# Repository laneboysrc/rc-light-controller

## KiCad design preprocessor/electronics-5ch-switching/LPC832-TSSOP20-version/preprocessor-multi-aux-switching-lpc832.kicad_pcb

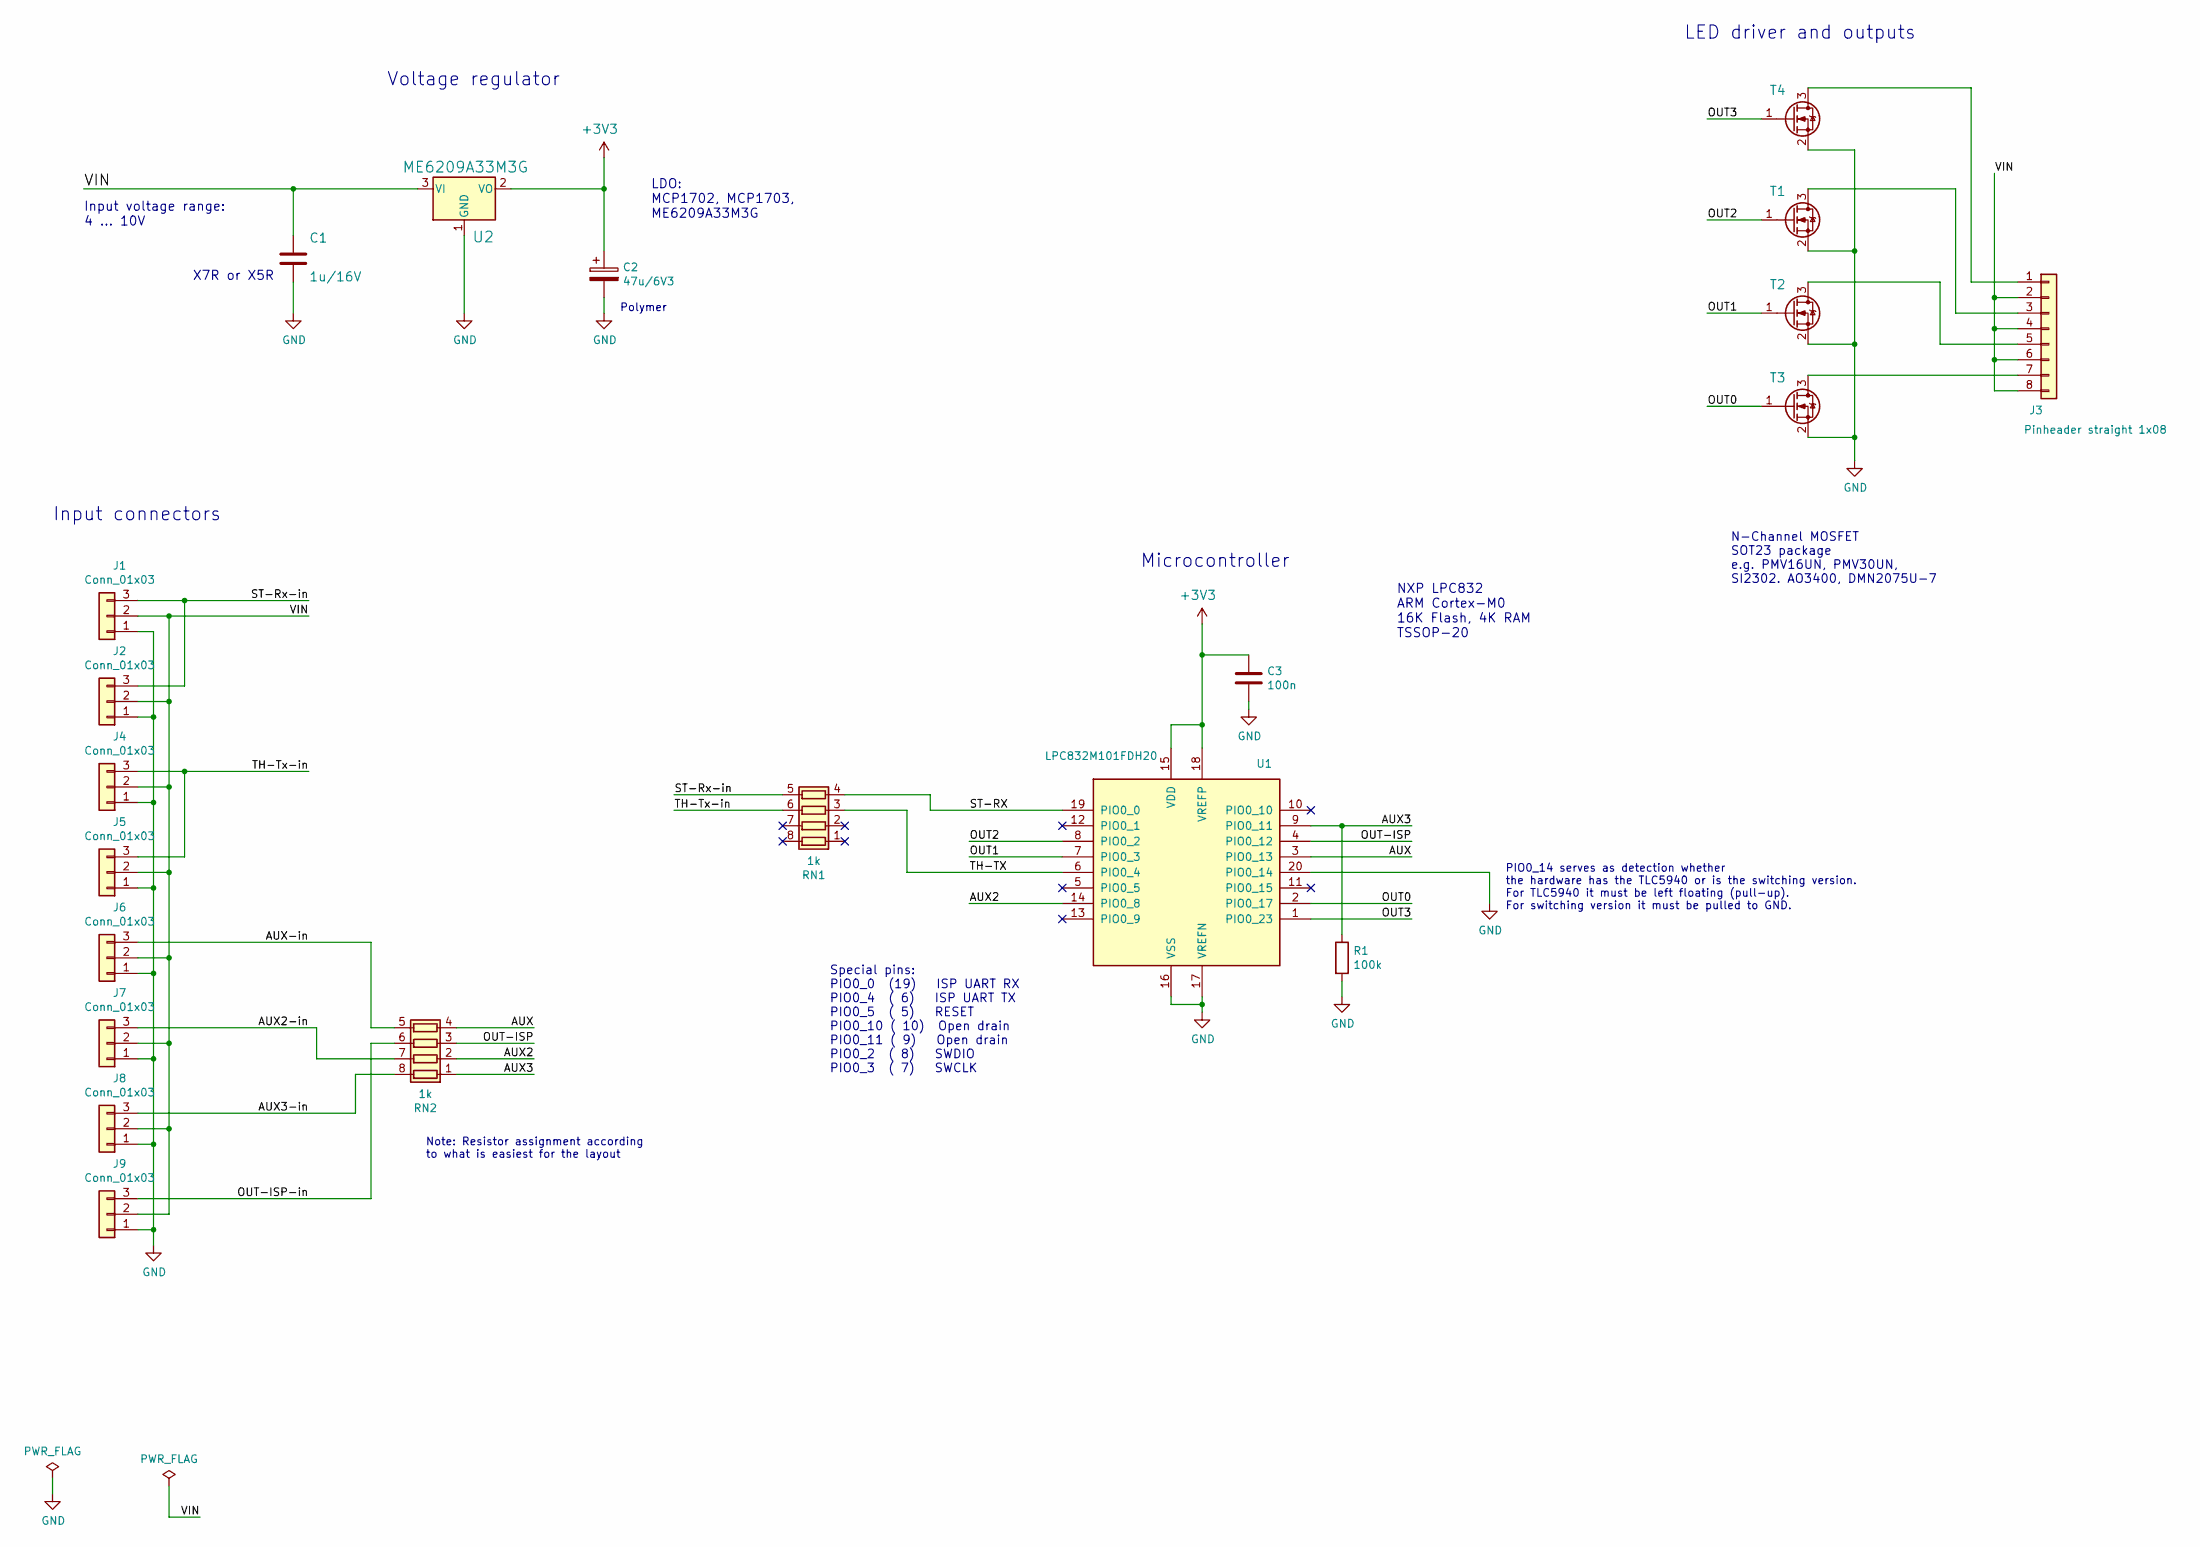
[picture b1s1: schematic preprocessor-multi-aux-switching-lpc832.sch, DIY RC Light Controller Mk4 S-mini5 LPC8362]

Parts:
C1: 1u/16V; C_0805_2012Metric
C2: 47u/6V3; C_0805_2012Metric
C3: 100n; C_0603_1608Metric
J1, J2, J4, J5, J6, J7, J8, J9: Conn_01x03; PinHeader_1x03_P2.54mm_Vertical_nosilk
J3: Pinheader straight 1x08; PinHeader_1x08_P2.54mm_Vertical_nosilk
R1: 100k; R_0603_1608Metric
RN1, RN2: 1k; R_Array_Convex_4x0603
T1, T2, T3, T4: PMV30UN; SOT-23
U1: LPC832M101FDH20; TSSOP-20_4.4x6.5mm_P0.65mm
U2: ME6209A33M3G; SOT-23W

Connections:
+3V3: C2.1, C3.1, U1.15 (VDD), U1.18 (VREFP), U2.2 (VO)
/AUX: RN2.4 (R4.1), U1.3 (PIO0_13)
/AUX2: RN2.2 (R2.1), U1.14 (PIO0_8)
/AUX2-in: J7.3, RN2.7 (R2.2)
/AUX3: R1.1, RN2.1 (R1.1), U1.9 (PIO0_11)
/AUX3-in: J8.3, RN2.8 (R1.2)
/AUX-in: J6.3, RN2.5 (R4.2)
/OUT0: T3.1 (G), U1.2 (PIO0_17)
/OUT1: T2.1 (G), U1.7 (PIO0_3)
/OUT2: T1.1 (G), U1.8 (PIO0_2)
/OUT3: T4.1 (G), U1.1 (PIO0_23)
/OUT-ISP: RN2.3 (R3.1), U1.4 (PIO0_12)
/OUT-ISP-in: J9.3, RN2.6 (R3.2)
/ST-RX: RN1.4 (R4.1), U1.19 (PIO0_0)
/ST-Rx-in: J1.3, J2.3, RN1.5 (R4.2)
/TH-TX: RN1.3 (R3.1), U1.6 (PIO0_4)
/TH-Tx-in: J4.3, J5.3, RN1.6 (R3.2)
/VIN: C1.1, J1.2, J2.2, J3.2, J3.4, J3.6, J3.8, J4.2, J5.2, J6.2, J7.2, J8.2, J9.2, U2.3 (VI)
GND: C1.2, C2.2, C3.2, J1.1, J2.1, J4.1, J5.1, J6.1, J7.1, J8.1, J9.1, R1.2, T1.2 (S), T2.2 (S), T3.2 (S), T4.2 (S), U1.16 (VSS), U1.17 (VREFN), U1.20 (PIO0_14), U2.1 (GND)
unnamed: J3.1, T4.3 (D)
unnamed: J3.3, T1.3 (D)
unnamed: J3.5, T2.3 (D)
unnamed: J3.7, T3.3 (D)

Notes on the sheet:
Special pins: PIO0_0 (19) ISP UART RX PIO0_4 ( 6) ISP UART TX PIO0_5 ( 5) RESET PIO0_10 ( 10) Open drain PIO0_11 ( 9) Open drain PIO0_2 ( 8) SWDIO PIO0_3 ( 7) SWCLK
Input connectors
Voltage regulator
Microcontroller
X7R or X5R
Input voltage range: 4 ... 10V
LDO: MCP1702, MCP1703, ME6209A33M3G
NXP LPC832 ARM Cortex-M0 16K Flash, 4K RAM TSSOP-20
N-Channel MOSFET SOT23 package e.g. PMV16UN, PMV30UN, SI2302. AO3400, DMN2075U-7
Polymer
LED driver and outputs
PIO0_14 serves as detection whether the hardware has the TLC5940 or is the switching version. For TLC5940 it must be left floating (pull-up). For switching version it must be pulled to GND.
Note: Resistor assignment according to what is easiest for the layout

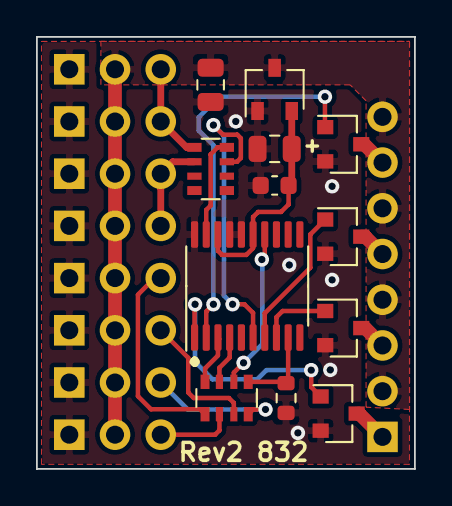
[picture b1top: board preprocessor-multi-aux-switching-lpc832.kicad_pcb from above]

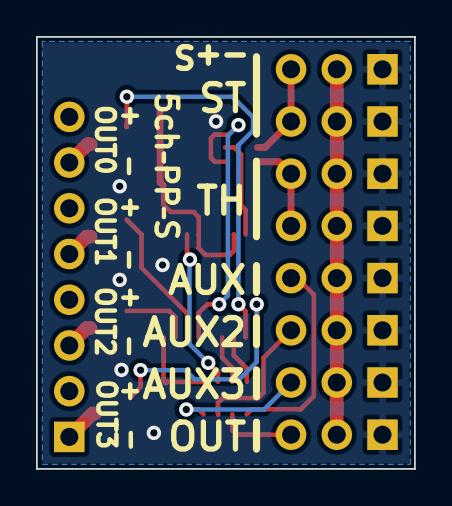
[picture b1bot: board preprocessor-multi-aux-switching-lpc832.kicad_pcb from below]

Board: 2 copper layers, 21.0 x 24.0 mm, 21 parts (9 on the bottom side), 23 nets.

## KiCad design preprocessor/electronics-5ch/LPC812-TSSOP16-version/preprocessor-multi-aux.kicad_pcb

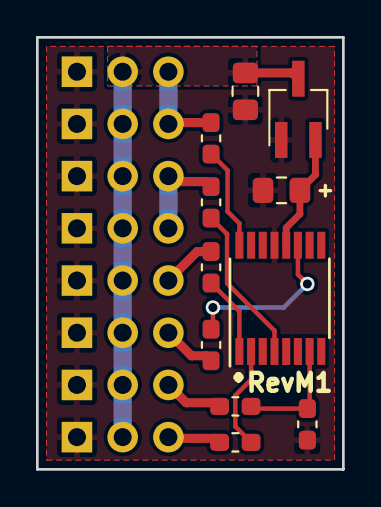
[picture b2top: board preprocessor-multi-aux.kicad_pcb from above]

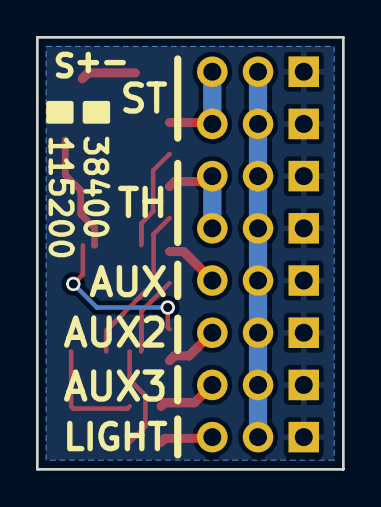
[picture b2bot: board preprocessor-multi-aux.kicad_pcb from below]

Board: 2 copper layers, 17.0 x 24.0 mm, 19 parts (8 on the bottom side), 15 nets.

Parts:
C1: 1u; C_0805_2012Metric_Pad1.15x1.40mm_HandSolder
C2: 47u/6V3 Polymer 0805; C_0805_2012Metric_Pad1.15x1.40mm_HandSolder
P1: ST-IN; PinHeader_1x03_P2.54mm_Vertical
P2: ST-OUT; PinHeader_1x03_P2.54mm_Vertical
P3: TH-IN; PinHeader_1x03_P2.54mm_Vertical
P4: TH-OUT; PinHeader_1x03_P2.54mm_Vertical
P5: AUX-IN; PinHeader_1x03_P2.54mm_Vertical
P6: LIGHT CONTROLLER; PinHeader_1x03_P2.54mm_Vertical
P7: AUX2-IN; PinHeader_1x03_P2.54mm_Vertical
P8: AUX3-IN; PinHeader_1x03_P2.54mm_Vertical
R1, R2, R3, R4, R5, R6: 1K; R_0603_1608Metric_Pad1.05x0.95mm_HandSolder
R7: 100k; R_0603_1608Metric_Pad1.05x0.95mm_HandSolder
U1: MCP1703T-3302E/CB; SOT-23W_Handsoldering
U2: LPC811M001JDH16_TSSOP16; TSSOP-16_4.4x5mm_P0.65mm

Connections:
+3V3: C2.1, U1.2, U2.12
/AUX: P5.3, R3.2
/AUX2: P7.3, R5.2
/AUX3: P8.3, R6.2
/LIGHT: P6.3, R4.1
/ST: P1.3, P2.3, R1.2
/TH: P3.3, P4.3, R2.2
GND: C1.2, C2.2, P1.1, P2.1, P3.1, P4.1, P5.1, P6.1, P7.1, P8.1, R7.1, U1.1, U2.13
unnamed: R1.1, U2.16
unnamed: R2.1, U2.4
unnamed: R3.1, U2.1
unnamed: R4.2, U2.2
unnamed: R5.1, U2.11
unnamed: R6.1, R7.2, U2.7
VCC: C1.1, P1.2, P2.2, P3.2, P4.2, P5.2, P6.2, P7.2, P8.2, U1.3

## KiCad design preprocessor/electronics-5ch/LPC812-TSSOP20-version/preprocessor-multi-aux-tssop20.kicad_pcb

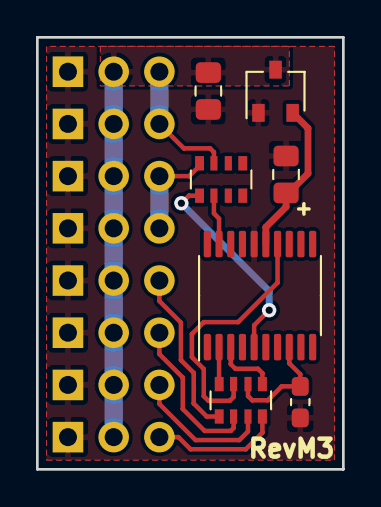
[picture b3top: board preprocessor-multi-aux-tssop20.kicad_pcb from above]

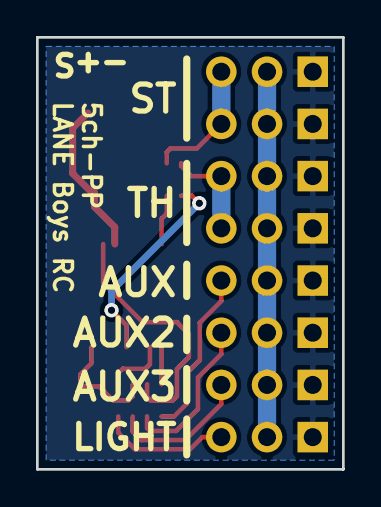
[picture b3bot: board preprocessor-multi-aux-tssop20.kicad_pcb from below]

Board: 2 copper layers, 17.0 x 24.0 mm, 15 parts (8 on the bottom side), 15 nets.

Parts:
C1: 1u; C_0805_2012Metric_Pad1.15x1.40mm_HandSolder
C2: 47u/6V3 Polymer 0805; C_0805_2012Metric_Pad1.15x1.40mm_HandSolder
P1: ST-IN; PinHeader_1x03_P2.54mm_Vertical
P2: ST-OUT; PinHeader_1x03_P2.54mm_Vertical
P3: TH-IN; PinHeader_1x03_P2.54mm_Vertical
P4: TH-OUT; PinHeader_1x03_P2.54mm_Vertical
P5: AUX-IN; PinHeader_1x03_P2.54mm_Vertical
P6: LIGHT CONTROLLER; PinHeader_1x03_P2.54mm_Vertical
P7: AUX2-IN; PinHeader_1x03_P2.54mm_Vertical
P8: AUX3-IN; PinHeader_1x03_P2.54mm_Vertical
R7: 100k; R_0603_1608Metric_Pad1.05x0.95mm_HandSolder
RN1, RN2: R_Pack04; R_Array_Convex_4x0603
U1: MCP1703T-3302E/CB; SOT-23W
U2: LPC812M101JDH20; TSSOP-20_4.4x6.5mm_P0.65mm

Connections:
+3V3: C2.1, U1.2, U2.15
/AUX: RN1.8, U2.2
/AUX2: RN1.7, U2.14
/AUX2_IN: P7.3, RN1.2
/AUX3: R7.2, RN1.6, U2.8
/AUX3_IN: P8.3, RN1.3
/AUX_IN: P5.3, RN1.1
/LIGHT: RN1.5, U2.3
/LIGHT_OUT: P6.3, RN1.4
/ST: RN2.6, U2.19
/ST_IN: P1.3, P2.3, RN2.3
/TH: RN2.5, U2.5
/TH_IN: P3.3, P4.3, RN2.4
GND: C1.2, C2.2, P1.1, P2.1, P3.1, P4.1, P5.1, P6.1, P7.1, P8.1, R7.1, U1.1, U2.16
VCC: C1.1, P1.2, P2.2, P3.2, P4.2, P5.2, P6.2, P7.2, P8.2, U1.3
